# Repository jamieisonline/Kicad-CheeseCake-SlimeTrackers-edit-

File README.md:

Edit of sorakage cheesecake slimevr trackers. For my personal use

Currently untested and still being updated with correct footprints

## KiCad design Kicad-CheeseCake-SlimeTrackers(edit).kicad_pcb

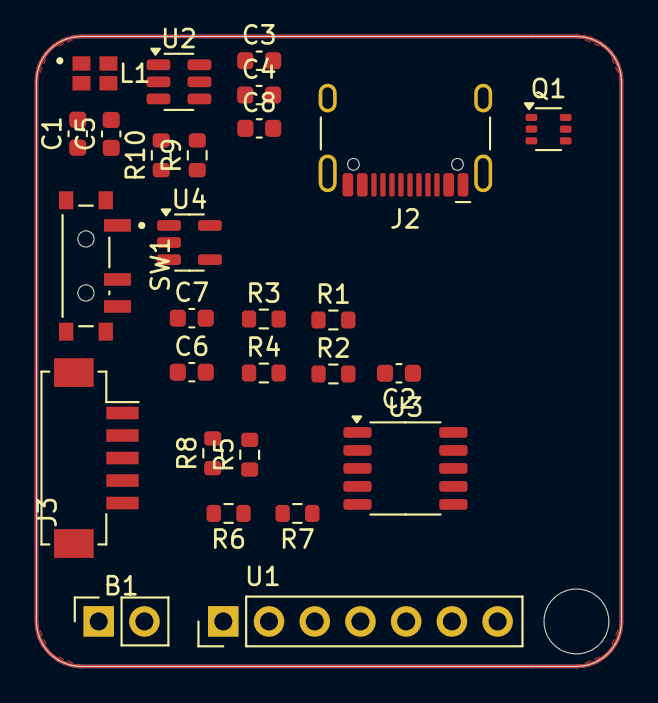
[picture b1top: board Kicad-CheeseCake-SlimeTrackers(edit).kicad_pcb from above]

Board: 2 copper layers, 32.5 x 35.0 mm, 29 parts (1 on the bottom side), 19 nets, no tracks yet.

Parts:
B1: HDR-M-2.54_1x2; PinSocket_1x02_P2.54mm_Vertical
C1: 10uF; C_0603_1608Metric
C2, C3, C7, C8: 100nF; C_0603_1608Metric
C4, C5, C6: 1uF; C_0603_1608Metric
ESP1: ESP-12F
J2: USB_C-16p; USB_C_Receptacle_HCTL_HC-TYPE-C-16P-01A
J3: 4P4C; Hirose_DF13C_CL535-0405-0-51_1x05-1MP_P1.25mm_Vertical
L1: NH-B2020RGBA-HF; LED_CLMVC-FKA-CG1H1A1BB7D3C3
Q1: UMH3N; SOT-363_SC-70-6
R1, R2: 5.1k; R_0603_1608Metric
R3: 180k; R_0603_1608Metric
R4: 3k; R_0603_1608Metric
R5, R6, R7, R8, R9, R10: 4.7k; R_0603_1608Metric
SW1: SW_SPDT; SW_SSSS811101
U1: ICM-45686; PinHeader_1x07_P2.54mm_Vertical
U2: TP4057; TSOT-23-6
U3: CH340K; SOIC-10_3.9x4.9mm_P1mm
U4: ME6211C33M5; SOT-23-5

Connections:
+3V3: C3.1, C4.1, C6.1, C7.1, C8.1, ESP1.8 (VCC), J3.1, R6.2, R7.2, R8.2, R9.2, R10.2, U1.2 (+3V3), U3.7 (VCC), U4.5 (V_{OUT})
+5V: L1.3, U2.4 (V_{CC})
BAT+: B1.1, C1.1, R3.1, SW1.1 (A), U2.3 (BAT)
DTR: Q1.2, Q1.4, U3.4 (~DTR)
EN: ESP1.3 (EN), R6.1
G: L1.4 (K), U2.5 (STDBY)
GND: B1.2, C1.2, C2.2, C3.2, C4.2, C5.2, C6.2, C7.2, C8.2, ESP1.9 (GND), J3.2, R1.2, R2.2, R4.1, R5.2, U1.3 (GND), U2.2 (GND), U3.3 (GND), U4.2 (V_{SS})
GPIO0: ESP1.12 (GPIO0), Q1.3, R8.1
GPIO15: ESP1.10 (GPIO15), R5.1
unnamed: R4.2, U2.6 (PROG)
unnamed: C2.1, U3.10 (V3)
R: L1.1 (K), U2.1 (~CHRG)
RST: ESP1.1 (RST), Q1.6, R7.1
RTS: Q1.1, Q1.5, U3.6 (~RTS)
RX: ESP1.15 (RXD0), U3.8 (TXD)
SCL: ESP1.14 (GPIO5), J3.3, R10.1, U1.4 (SCL)
SDA: ESP1.13 (GPIO4), J3.4, R9.1, U1.5 (SDA)
TX: ESP1.16 (TXD0), U3.9 (RXD)
VIN: C5.1, SW1.2 (B), U4.1 (V_{IN}), U4.3 (CE)

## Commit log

2025-07-05 h
    h
2025-07-05 updt
2025-07-06 inital footprint assignment
    erc tests passed
    some potential issues regarding +3v3 flag - cleared tests for now
    some footprints could be wrong and are placeholder
2025-07-06 started pcb
    pcb inital
2025-07-06 updt
    lots of fixes to footprints
2025-07-06 fixes
    board will be 33x35 or bigger
2025-07-06 updt
    updt
